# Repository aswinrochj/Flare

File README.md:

# SAFE-NODE — Fail-Safe Real-Time Gas and Fire Safety Network

**Team NEXUS · Team ID M2026-133 · St. Joseph's College of Engineering, Chennai**
VConnecTech Engineering Marathon 2026

SAFE-NODE is a low-cost gas, flame and heat safety network built on the ESP32. Its design rule is that **the system must never fail silently**. An unplugged sensor, a hung controller or a dead radio link is reported as a fault or an offline node, never as "safe".

> **Safety notice.** SAFE-NODE is a student prototype. It is not a certified gas detector (IS/IEC 60079-29-1) or fire alarm (IS 2189), and it must not replace one.

## Documents

| Document | Standard followed | Contents |
|---|---|---|
| [`docs/M2026-133_FailSafeGasFireNetwork_DPR.pdf`](docs/M2026-133_FailSafeGasFireNetwork_DPR.pdf) | Marathon DPR template, IEEE two-column | Problem, objectives O1–O6, design, plan, results |
| [`docs/M2026-133_SAFE-NODE_Technical_Documentation.pdf`](docs/M2026-133_SAFE-NODE_Technical_Documentation.pdf) | IEEE Std 1016 (design), IEEE Std 829 (test) | Schematic, PCB, pin map, BOM, firmware, protocol, test log, anomaly reports |
| [`docs/SRS.md`](docs/SRS.md) | ISO/IEC/IEEE 29148 | Requirements with IDs, traced to objectives and test cases |
| [`test/test-plan.md`](test/test-plan.md) | IEEE Std 829 | Test plan and test case specifications |
| [`test/logs/`](test/logs/) | IEEE Std 829 | Dated test logs and incident reports |
| [`hardware/README.md`](hardware/README.md) | IEEE Std 315, IPC-2221B | KiCad project, fabrication and assembly notes |
| [`docs/references.bib`](docs/references.bib) | IEEE reference style | Bibliography in BibTeX |

## Status (25 November 2026)

| Part | Status |
|---|---|
| Node circuit | Simulated in LabWired. See [`simulation/`](simulation/) |
| Carrier PCB rev 1.0 | KiCad 7 schematic and 2-layer layout complete. DRC shows 0 unconnected pads and 0 clearance errors. Gerbers are ready but no board has been built yet |
| Firmware v0.1 (Arduino) | Runs in simulation. Gas and flame inputs are sampled; a hazard turns on the red LED and buzzer, and a fault turns on the yellow LED |
| Firmware v1.0 (ESP-IDF, FreeRTOS, watchdog, LoRa) | Code complete; builds with ESP-IDF v5.2.3 (no warnings); decision logic unit-tested on a PC. **Not yet run on hardware** |
| Gateway firmware | Code complete; builds with ESP-IDF v5.2.3 (no warnings); node table unit-tested. **Not yet run on hardware** |
| Host: MQTT bridge, SQLite, dashboard, SMS | Complete and tested end to end against a gateway emulator. Not yet run with a real gateway |
| Bench tests TC-1 to TC-9 | Planned for the Implementation Round; scripts in [`test/scripts/`](test/scripts/) |

Open issues are tracked as AR-1 … AR-12 in Section VI-E of the technical documentation. AR-1 and AR-8 are closed in the PCB. AR-2 to AR-7 and AR-10 are addressed in the firmware v1.0 code; they stay open until the bench tests confirm the fixes. Before powering real hardware, read [`hardware/README.md`](hardware/README.md).

## Simulation

| Project | Link |
|---|---|
| `final`: complete node circuit | https://app.labwired.com/p/dharshinir2028/b2b2b0950f8219b71e729534c77f84a7 |
| `final_slider_monitor`: same circuit with slide potentiometers on GPIO32/33 | https://app.labwired.com/p/963436e296210af24c3ec1ab57304f01 |

How to run it and what was verified: [`simulation/README.md`](simulation/README.md).

## Hardware at a glance

| Signal | ESP32 pin | Notes |
|---|---|---|
| MQ-2 AO | GPIO32 (ADC1_CH4) | Through an R1 = 12 kΩ / R2 = 10 kΩ divider (5 V → 2.27 V) |
| Flame AO | GPIO33 (ADC1_CH5) | Module powered from 3V3 |
| DHT22 DATA | GPIO4 | R7 = 10 kΩ pull-up. Read at most once every 2 s |
| Buzzer | GPIO13 | PN2222A low-side driver, R6 = 1 kΩ, D4 flyback |
| LED red / green / yellow | GPIO14 / 16 / 17 | 220 Ω each, for hazard / healthy / fault |
| Battery sense | GPIO35 (ADC1_CH7) | 100 kΩ / 100 kΩ divider |
| RFM95W (SX1276) LoRa | SCK 18, MISO 19, MOSI 23, NSS 5, RST 27, DIO0 26 | 865–867 MHz only (India licence-exempt band) |

Board: 100 × 75 mm, 2 layers. Indicative cost is about ₹2,460 per node (see [`hardware/fab/safe-node-bom.csv`](hardware/fab/safe-node-bom.csv)).

## Quick start (no hardware needed)

```bash
git clone <this repository> && cd safe-node-m2026-133
python3 -m venv .venv && source .venv/bin/activate    # Windows: .venv\Scripts\activate
pip install -r host/requirements-dev.txt
make test        # firmware unit tests (gcc) + host tests (pytest)
make budget      # reproduce the analytical figures of DPR Table X
make demo        # host + emulated gateway with three nodes -> http://127.0.0.1:5000
```

Without `make` (for example on Windows): `cd host && python -m pytest -q`, then `python -m safenode_host --demo --no-mqtt`.

## Repository layout

```
.
├── docs/                 DPR, technical documentation, SRS, figures, references.bib
├── hardware/
│   ├── kicad/            KiCad 7 project (schematic, PCB, symbols, footprints, netlist)
│   ├── fab/              Gerber X2 + Excellon, zipped Gerbers, BOM, placement file
│   ├── plots/            Schematic PDF/PNG, PCB top/bottom/assembly renders
│   └── reports/          KiCad DRC report
├── simulation/           LabWired project links, run procedure, screenshots
├── firmware/
│   ├── node/v0.1/        Arduino prototype (as simulated in LabWired)
│   ├── node/v1.0/        ESP-IDF + FreeRTOS target firmware
│   ├── gateway/          Gateway ESP32 + SX1276
│   ├── components/       Shared: frame protocol, SX1276 driver, board pin map
│   └── test/             Unit tests for the firmware logic (run on a PC)
├── host/                 Serial→MQTT bridge, SQLite, Flask dashboard, SMS queue, gateway emulator
├── test/                 Test plan, dated test logs, log template, test scripts, protocol vectors
├── tools/                DPR budget calculator, vector generator, pcbgen (schematic/PCB generator)
├── .github/              CI workflow, anomaly-report and change-request templates
├── Makefile              test / demo / budget / node / gateway targets
├── LICENSES/             Full licence texts
├── CITATION.cff  CHANGELOG.md  CONTRIBUTING.md  CODE_OF_CONDUCT.md
```

## Dependencies

| Part | Tools and libraries |
|---|---|
| Firmware v0.1 | Arduino IDE 2, *esp32* board package by Espressif |
| Firmware v1.0, gateway | ESP-IDF v5.2 or later (includes FreeRTOS); CI uses v5.2.3 |
| Firmware unit tests | A C99 compiler (`gcc` or `clang`) and `make` |
| Host | Python 3.10+, packages in [`host/requirements.txt`](host/requirements.txt) (`paho-mqtt`, `flask`, `pyserial`, `requests`); Mosquitto MQTT broker (optional); Twilio account for SMS (optional) |
| Hardware | KiCad 7 or later |
| `tools/pcbgen` | KiCad 7 `pcbnew` Python module, Python 3.10+, `numpy` |
| Simulation | Web browser (LabWired, links above) |

## Build and run

**Firmware v0.1 (Arduino):** see [`firmware/node/v0.1/README.md`](firmware/node/v0.1/README.md). In Arduino IDE 2, install the *esp32* board package, open `firmware/node/v0.1/main/main.ino`, select *ESP32 Dev Module* and upload. Serial Monitor at 115200 baud; test commands `G<n>`, `F<n>`, `T<n>`, `H<n>`, `X`/`Y`/`Z`, `R`, `?`.

**Firmware v1.0 and gateway (ESP-IDF v5):**
```bash
. $IDF_PATH/export.sh
cd firmware/node/v1.0             # set a unique node ID in menuconfig -> "SAFE-NODE node"
idf.py set-target esp32
idf.py menuconfig
idf.py build flash monitor
cd ../../gateway && idf.py set-target esp32 build flash
```
Details: [`firmware/node/v1.0/README.md`](firmware/node/v1.0/README.md), [`firmware/gateway/README.md`](firmware/gateway/README.md).

**Host:**
```bash
cd host && pip install -r requirements.txt
python bridge.py --port /dev/ttyUSB0 --config config.example.json     # dashboard at http://127.0.0.1:5000
```
Details: [`host/README.md`](host/README.md).

**Hardware:** open `hardware/kicad/safe-node.kicad_pro` in KiCad 7 or later. To order boards, send `hardware/fab/safe-node-gerbers.zip` to any PCB maker. Settings: 2 layers, 1.6 mm FR-4, HASL.

**Continuous integration:** every push runs the unit tests, checks the protocol vectors and the DPR budget, builds both ESP-IDF projects with ESP-IDF v5.2.3, and compiles the v0.1 sketch ([`.github/workflows/ci.yml`](.github/workflows/ci.yml)).

## Requirement coverage in code

| Objective | Requirements | Implemented in | Verified by (today) |
|---|---|---|---|
| O1 local alarm | FR-01, FR-03–FR-06, PR-01 | `firmware/node/v1.0/main/classifier.c`, `main.c` (sensor, alarm tasks) | `firmware/test/test_classifier.c`; SIM-2 (v0.1) |
| O2 remote alert | FR-22–FR-25, PR-02 | `firmware/node/v1.0/main/radio.c`, `firmware/gateway/`, `host/` | `host/tests/`; analysis `tools/lora_budget.py` |
| O3 offline detection | FR-20, FR-21 | `heartbeat_task`, `firmware/gateway/main/node_table.c` | `test_node_table.c`, `host/tests/test_end_to_end.py` |
| O4 hang recovery | FR-14, FR-15 | `health_task` (conditional watchdog feed), RTC reset counter, NVS event ring | TC-4 on the bench (planned) |
| O5 sensor faults | FR-02, FR-10–FR-13 | `classifier.c`, `selftest.c`, `dht22.c` | `test_classifier.c` |
| O6 cost, backup, isolation | FR-16, PR-03, PR-04, HR-06 | Task priorities and core pinning, low-battery rule | BOM; `tools/lora_budget.py`; TC-6, TC-8 (planned) |

## Team

| Member | Role |
|---|---|
| Dharshini R (Team Lead) | Firmware, RTOS, watchdog, test lead |
| Dheekshitha R | Hardware, power, sensor interfacing |
| Aswin Roch J | LoRa / ESP-NOW, protocol, gateway |
| Anto Prisin D | MQTT bridge, dashboard, SMS |

## Licence

| Part | Licence |
|---|---|
| Firmware, host software, `tools/` | MIT ([`LICENSE`](LICENSE)) |
| Hardware design files (`hardware/`) | CERN-OHL-P-2.0 ([`LICENSES/CERN-OHL-P-2.0.txt`](LICENSES/CERN-OHL-P-2.0.txt)) |
| Documentation (`docs/`, `test/`, `simulation/`) | CC BY 4.0 ([`LICENSES/CC-BY-4.0.txt`](LICENSES/CC-BY-4.0.txt)) |

To cite this work, see [`CITATION.cff`](CITATION.cff).

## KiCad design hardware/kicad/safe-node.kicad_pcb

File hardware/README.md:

# SAFE-NODE carrier board, rev 1.0: hardware documentation

The carrier PCB holds one sensor node: an ESP32-DevKitC V4 in sockets, an RFM95W (SX1276) LoRa module, connectors for the MQ-2, flame and DHT22 modules, a 5 V power input, battery sensing, status LEDs and a buzzer driver.

- Schematic, drawn in KiCad 7 with class letters per IEEE Std 315: [`plots/safe-node-schematic.pdf`](plots/safe-node-schematic.pdf)
- PCB layout, 2-layer, IPC-2221B clearances: [`kicad/safe-node.kicad_pcb`](kicad/safe-node.kicad_pcb)
- Design rationale (divider values, power budget, driver sizing): Section III of [`../docs/M2026-133_SAFE-NODE_Technical_Documentation.pdf`](../docs/M2026-133_SAFE-NODE_Technical_Documentation.pdf)

## Simulation links

The circuit on this board was first simulated in LabWired:

| Project | Link | Contents |
|---|---|---|
| `final` | https://app.labwired.com/p/dharshinir2028/b2b2b0950f8219b71e729534c77f84a7 | Complete node circuit: ESP32, MQ-2, flame, DHT22, buzzer driver, LEDs |
| `final_slider_monitor` | https://app.labwired.com/p/963436e296210af24c3ec1ab57304f01 | Same circuit, with slide potentiometers driving GPIO32/33. Firmware v0.1. Electrical check passed |

Changes from the simulated circuit to this PCB:

| Change | Reason |
|---|---|
| MQ-2 AO goes through R1 = 12 kΩ / R2 = 10 kΩ to GPIO32 | Closes AR-1. Without the divider, up to 5 V reaches a 3.3 V pin |
| Buzzer base resistor raised from 220 Ω to 1 kΩ | Closes AR-8. 2.6 mA base current still saturates the PN2222A |
| LEDs changed to red, green and yellow | Closes AR-8 |
| Added: RFM95W, SMA connector, 5 V input with D5 reverse-polarity protection, JP1, battery sense, decoupling and ADC filter capacitors | Not modelled in the simulation |

Because of the divider, the gas threshold of 1800 counts used in the simulation must be recalibrated for hardware.

## Files

| Path | Contents |
|---|---|
| `kicad/safe-node.kicad_pro` | KiCad 7 project. Open this file |
| `kicad/safe-node.kicad_sch` | Schematic, single A3 sheet |
| `kicad/safe-node.kicad_pcb` | PCB layout: 100 × 75 mm, 2 layers |
| `kicad/safe-node.kicad_sym`, `kicad/safe-node.pretty/` | Project symbol and footprint libraries. The tables reference them through `${KIPRJMOD}` |
| `kicad/safe-node.net` | Exported netlist: 36 parts, 27 nets |
| `fab/gerbers/` | Gerber X2 layers, Excellon PTH/NPTH drill files and drill maps, `.gbrjob` |
| `fab/safe-node-gerbers.zip` | Same files, zipped for upload to a PCB maker |
| `fab/safe-node-bom.csv` | Grouped bill of materials, with function and indicative INR cost for each line |
| `fab/safe-node-pos.csv` | Component placement file |
| `plots/` | Schematic PDF and PNG; PCB top, bottom and assembly renders (PNG, SVG, PDF) |
| `reports/drc.rpt` | KiCad design-rule-check report |

All other footprints come from the standard KiCad 7 libraries.

## Board data

| Item | Value |
|---|---|
| Size and stack-up | 100 × 75 mm, 2 layers, FR-4 1.6 mm, 1 oz copper |
| Clearance / edge clearance | 0.2 mm / 0.3 mm |
| Track width | 0.3 mm signal, 0.6 mm power, 1.0 mm RF (ANT) |
| Vias | 0.8 mm pad, 0.4 mm drill (18 in total) |
| Ground | GND pour on both layers, with thermal reliefs |
| Mounting | 4 × M3 (3.2 mm) holes at the corners |
| Routing | 400 track segments, 1.25 m of track |

## Design-rule check

DRC was run in KiCad 7 (`reports/drc.rpt`).

| Result | Count | Disposition |
|---|---|---|
| Unconnected pads | 0 | — |
| Clearance / short errors | 0 | — |
| Footprint errors | 0 | — |
| `copper_edge_clearance` | 5 | Accepted. J1 is an edge-mount SMA connector and must sit on the board edge |
| `silk_overlap` | 4 | Cosmetic. Reference text touches outline silkscreen; legible on the plots |
| `lib_footprint_issues` | 35 | Environment only. The DRC machine had no global KiCad footprint table. These warnings disappear on a normal KiCad install |

The schematic netlist was compared with the source netlist in `tools/pcbgen/netlist.py`: 27 of 27 nets matched, with 0 differences. The board was routed by the grid router in `tools/pcbgen/router.py`, and every result was then checked with KiCad's own DRC.

## Before you order or power the board

1. **Measure the DevKit row spacing.** The footprint assumes the two 1×19 header rows are 25.4 mm (1.0 in) apart, as on the Espressif ESP32-DevKitC V4. Some clone boards use 22.86 mm or 27.94 mm. Hold the board against a 1:1 print of `plots/pcb-top.pdf` before ordering.
2. **Set the 5 V supply to 5.4 V.** The MQ-2 heater needs 5.0 ± 0.1 V, and D5 (1N5819) drops 0.3–0.45 V. With an adjustable boost module (MT3608), set its output to about 5.4 V, then measure 4.9–5.1 V at J2 pin 1.
3. **Use one power source at a time.** The DevKitC must have only one supply. JP1 joins the board's 5 V rail to the DevKit 5V pin. **Remove JP1 whenever a USB cable is plugged into the DevKit.**
4. **Check the MQ-2 module pin order** against J2 (pin 1 VCC, 2 GND, 3 DO, 4 AO) before plugging it in. DO is not connected.
5. **Connect the antenna before transmitting.** Fit an 865–867 MHz antenna to J1 before running any LoRa firmware.
6. **Check flame-module polarity.** Some modules pull AO low when they see a flame. Confirm on the real module before setting the comparison direction in firmware (AR-9).

## Assembly order

1. Low parts first: resistors R1–R9, diodes D4 and D5 (check the band), and capacitors C3–C7.
2. Then the RFM95W (U2, SMD castellations, hand-solderable with a fine tip), followed by the SMA connector J1.
3. Then Q1 (check the flat face against the silkscreen), the LEDs D1–D3 (long lead = anode, square pad = cathode), the buzzer BZ1 (+ to the 5V pad), and electrolytics C1 and C2 (observe polarity).
4. Last, the two 1×19 female sockets for U1, the pin headers J2–J4, JP1, and the terminal blocks J5 and J6.
5. Before inserting the DevKit, power J5 and check: 5 V at JP1 pin 1; with JP1 fitted and the DevKit inserted, 3.3 V on the +3V3 net; no more than 2.3 V at GPIO32 with the MQ-2 fitted.

## Regenerating the design

The schematic and PCB are generated from one netlist (`tools/pcbgen/netlist.py`). See [`../tools/pcbgen/README.md`](../tools/pcbgen/README.md). If you edit them by hand in KiCad, stop using the generator, or your edits will be overwritten.

## Licence

The hardware design files in this directory are licensed under CERN-OHL-P-2.0 (see [`../LICENSES/CERN-OHL-P-2.0.txt`](../LICENSES/CERN-OHL-P-2.0.txt)).

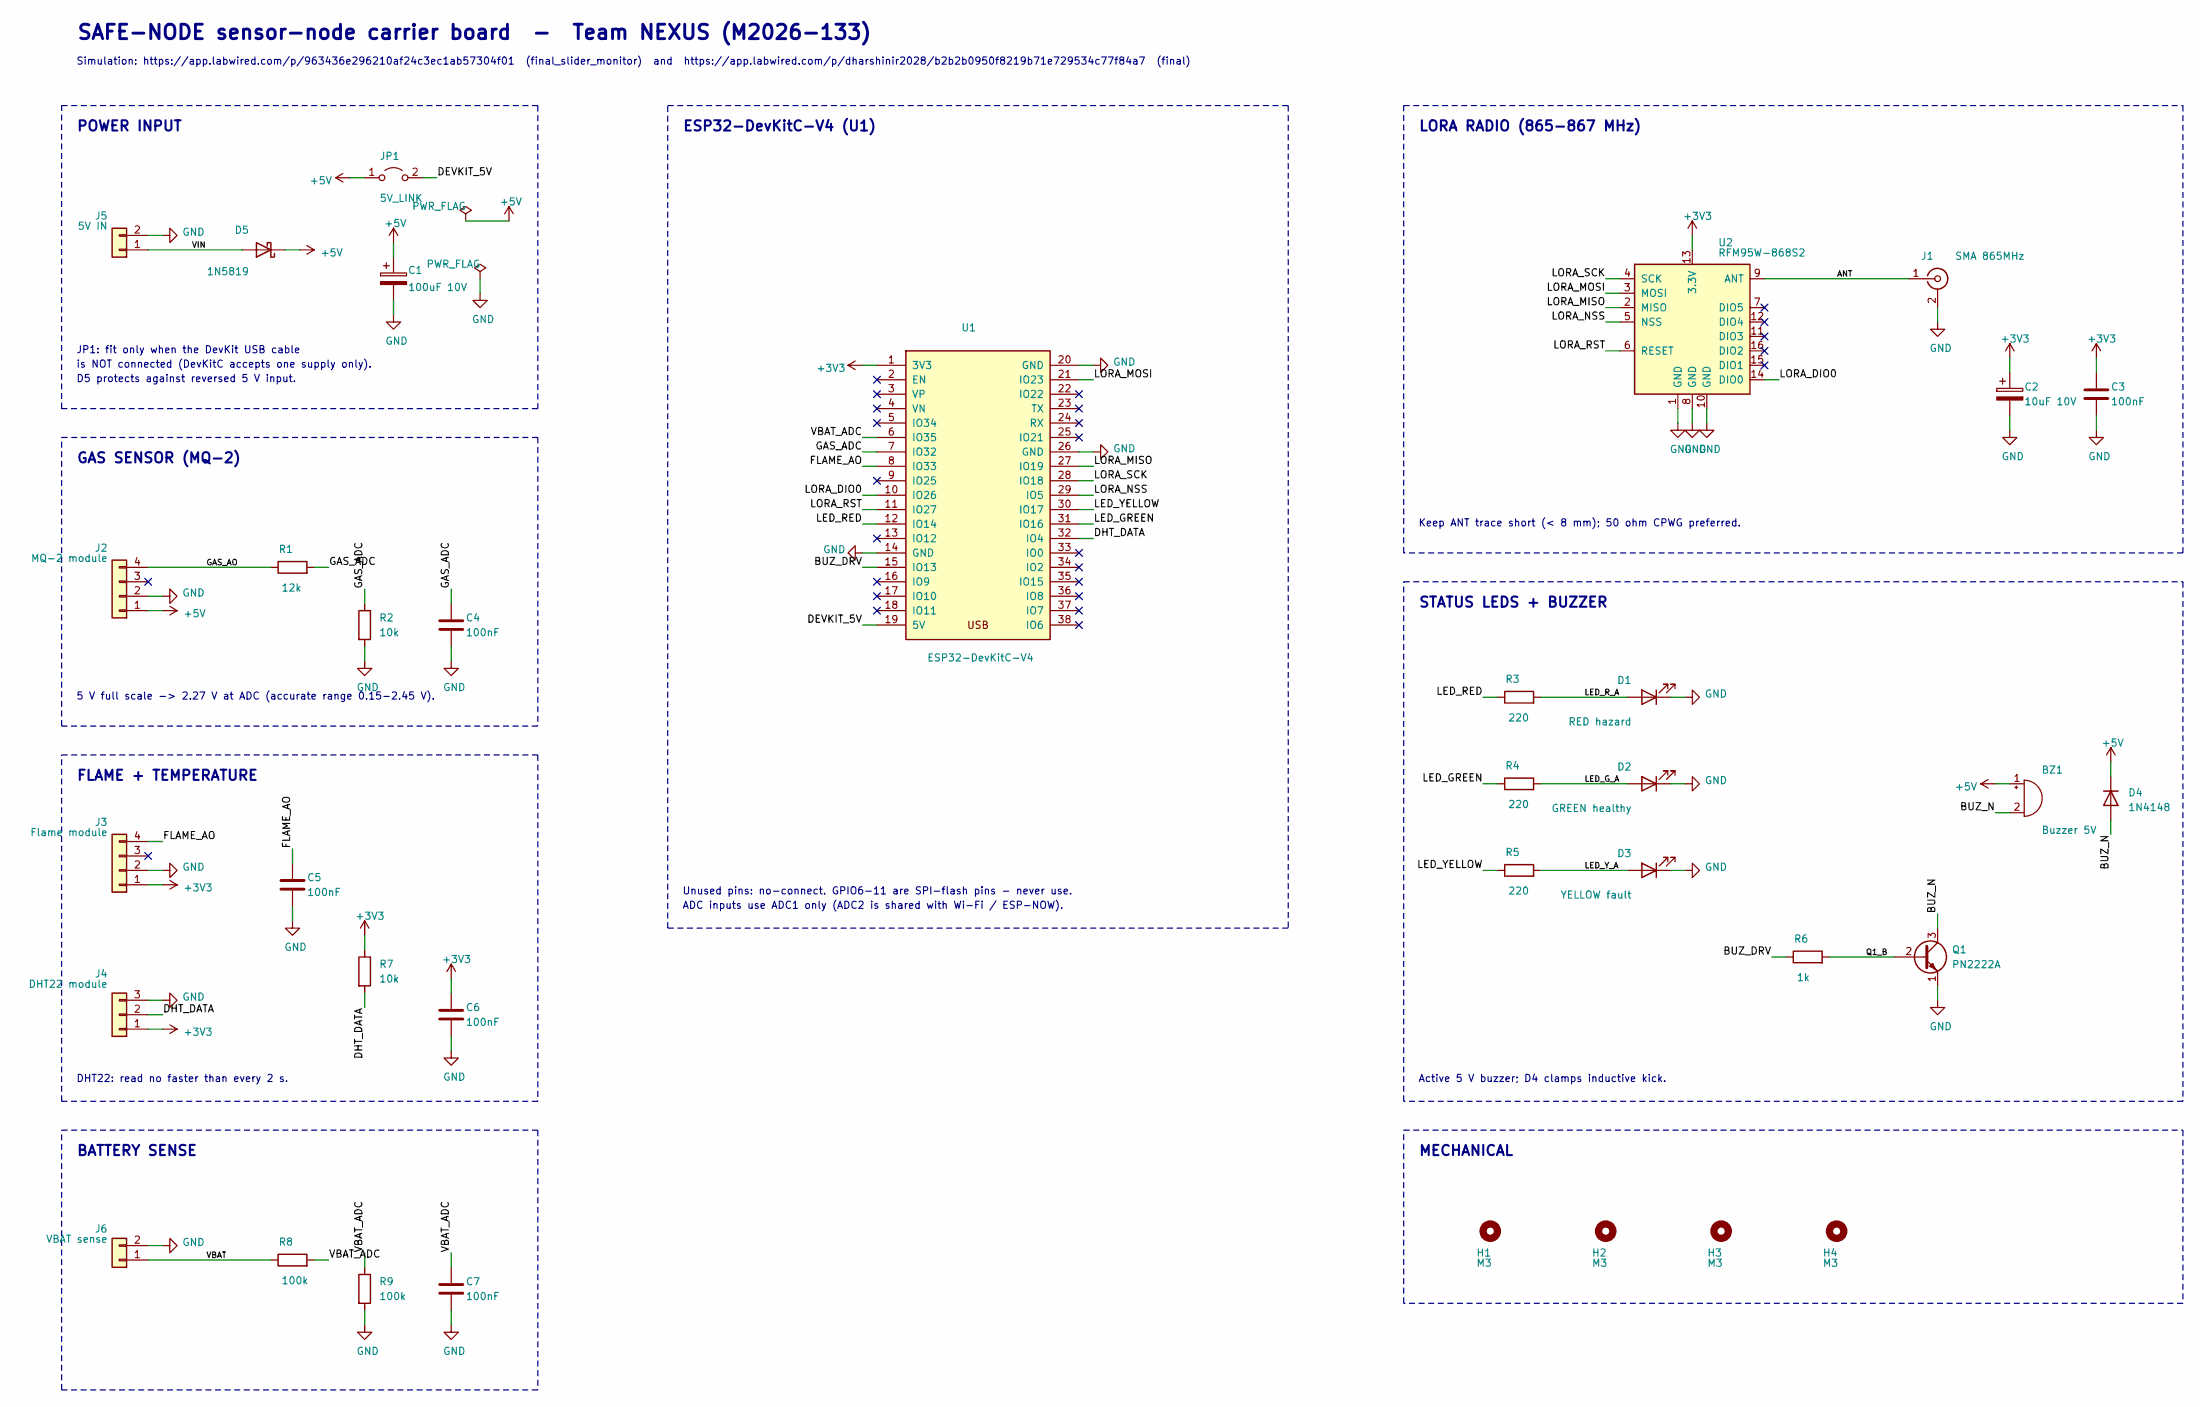
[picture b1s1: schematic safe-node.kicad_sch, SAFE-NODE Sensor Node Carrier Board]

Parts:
BZ1: Buzzer 5V; Buzzer_12x9.5RM7.6
C1: 100uF 10V; CP_Radial_D6.3mm_P2.50mm
C2: 10uF 10V; CP_Radial_D5.0mm_P2.00mm
C3, C4, C5, C6, C7: 100nF; C_Disc_D3.0mm_W1.6mm_P2.50mm
D1: RED hazard; LED_D5.0mm
D2: GREEN healthy; LED_D5.0mm
D3: YELLOW fault; LED_D5.0mm
D4: 1N4148; D_DO-35_SOD27_P7.62mm_Horizontal
D5: 1N5819; D_DO-41_SOD81_P10.16mm_Horizontal
H1, H2, H3, H4: M3; MountingHole_3.2mm_M3
J1: SMA 865MHz; SMA_Amphenol_132289_EdgeMount
J2: MQ-2 module; PinHeader_1x04_P2.54mm_Vertical
J3: Flame module; PinHeader_1x04_P2.54mm_Vertical
J4: DHT22 module; PinHeader_1x03_P2.54mm_Vertical
J5: 5V IN; TerminalBlock_bornier-2_P5.08mm
J6: VBAT sense; PinHeader_1x02_P2.54mm_Vertical
JP1: 5V_LINK; PinHeader_1x02_P2.54mm_Vertical
Q1: PN2222A; TO-92_Inline
R1: 12k; R_Axial_DIN0207_L6.3mm_D2.5mm_P7.62mm_Horizontal
R2, R7: 10k; R_Axial_DIN0207_L6.3mm_D2.5mm_P7.62mm_Horizontal
R3, R4, R5: 220; R_Axial_DIN0207_L6.3mm_D2.5mm_P7.62mm_Horizontal
R6: 1k; R_Axial_DIN0207_L6.3mm_D2.5mm_P7.62mm_Horizontal
R8, R9: 100k; R_Axial_DIN0207_L6.3mm_D2.5mm_P7.62mm_Horizontal
U1: ESP32-DevKitC-V4; ESP32-DevKitC-V4_Socket
U2: RFM95W-868S2; HOPERF_RFM9XW_SMD

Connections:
+3V3: C2.1, C3.1, C6.1, J3.1, J4.1, R7.1, U1.1 (3V3), U2.13 (3.3V)
+5V: BZ1.1 (+), C1.1, D4.1 (K), D5.1 (K), J2.1, JP1.1 (A)
ANT: J1.1 (In), U2.9 (ANT)
BUZ_DRV: R6.1, U1.15 (IO13)
BUZ_N: BZ1.2 (-), D4.2 (A), Q1.3 (C)
DEVKIT_5V: JP1.2 (B), U1.19 (5V)
DHT_DATA: J4.2, R7.2, U1.32 (IO4)
FLAME_AO: C5.1, J3.4, U1.8 (IO33)
GAS_ADC: C4.1, R1.2, R2.1, U1.7 (IO32)
GAS_AO: J2.4, R1.1
GND: C1.2, C2.2, C3.2, C4.2, C5.2, C6.2, C7.2, D1.1 (K), D2.1 (K), D3.1 (K), J1.2 (Ext), J2.2, J3.2, J4.3, J5.2, J6.2, Q1.1 (E), R2.2, R9.2, U1.14 (GND), U1.20 (GND), U1.26 (GND), U2.1 (GND), U2.8 (GND), U2.10 (GND)
LED_GREEN: R4.1, U1.31 (IO16)
LED_G_A: D2.2 (A), R4.2
LED_RED: R3.1, U1.12 (IO14)
LED_R_A: D1.2 (A), R3.2
LED_YELLOW: R5.1, U1.30 (IO17)
LED_Y_A: D3.2 (A), R5.2
LORA_DIO0: U1.10 (IO26), U2.14 (DIO0)
LORA_MISO: U1.27 (IO19), U2.2 (MISO)
LORA_MOSI: U1.21 (IO23), U2.3 (MOSI)
LORA_NSS: U1.29 (IO5), U2.5 (NSS)
LORA_RST: U1.11 (IO27), U2.6 (RESET)
LORA_SCK: U1.28 (IO18), U2.4 (SCK)
Q1_B: Q1.2 (B), R6.2
VBAT: J6.1, R8.1
VBAT_ADC: C7.1, R8.2, R9.1, U1.6 (IO35)
VIN: D5.2 (A), J5.1

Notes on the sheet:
SAFE-NODE sensor-node carrier board - Team NEXUS (M2026-133)
Simulation: https://app.labwired.com/p/963436e296210af24c3ec1ab57304f01 (final_slider_monitor) and https://app.labwired.com/p/dharshinir2028/b2b2b0950f8219b71e729534c77f84a7 (final)
POWER INPUT
JP1: fit only when the DevKit USB cable
is NOT connected (DevKitC accepts one supply only).
D5 protects against reversed 5 V input.
ESP32-DevKitC-V4 (U1)
Unused pins: no-connect. GPIO6-11 are SPI-flash pins - never use.
ADC inputs use ADC1 only (ADC2 is shared with Wi-Fi / ESP-NOW).
GAS SENSOR (MQ-2)
5 V full scale -> 2.27 V at ADC (accurate range 0.15-2.45 V).
FLAME + TEMPERATURE
DHT22: read no faster than every 2 s.
BATTERY SENSE
LORA RADIO (865-867 MHz)
Keep ANT trace short (< 8 mm); 50 ohm CPWG preferred.
STATUS LEDS + BUZZER
Active 5 V buzzer; D4 clamps inductive kick.
MECHANICAL

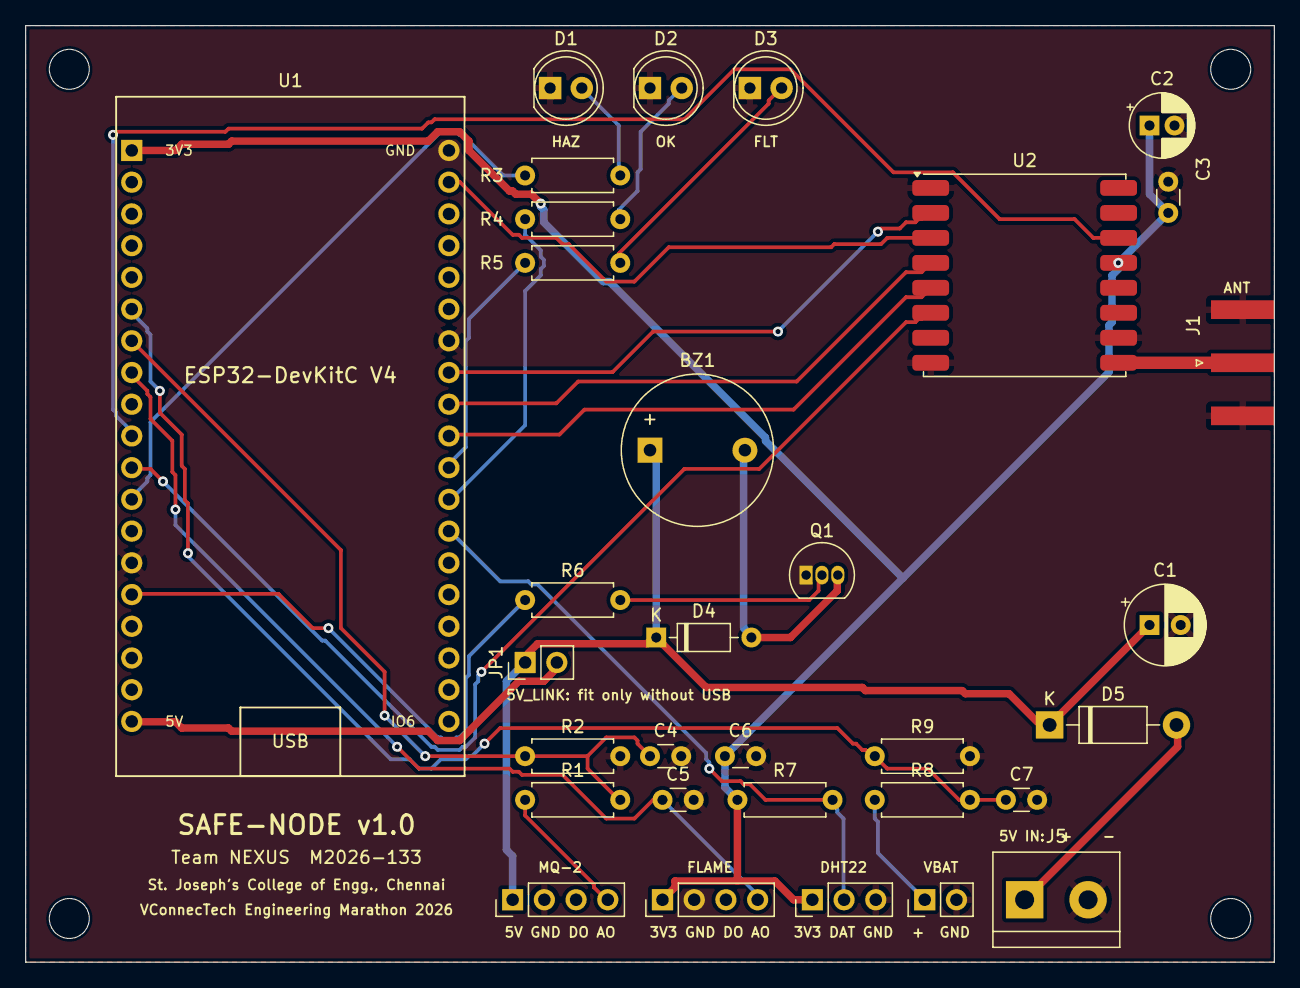
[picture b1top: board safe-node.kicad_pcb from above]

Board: 2 copper layers, 100.0 x 75.0 mm, 36 parts (0 on the bottom side), 27 nets.

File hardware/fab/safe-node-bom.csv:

Item,References,Qty,Value,Footprint,Function,Indicative cost INR (Nov 2026),Notes
1,U1,1,ESP32-DevKitC-V4,ESP32-DevKitC-V4_Socket,"Espressif ESP32-DevKitC V4 (WROOM-32) on 2x19 female sockets, rows 25.4 mm apart",450,"Two 1x19 2.54 mm female sockets, rows 25.4 mm apart"
2,U2,1,RFM95W-868S2,HOPERF_RFM9XW_SMD,"HopeRF SX1276 LoRa module, operated at 865-867 MHz",690,
3,J1,1,SMA 865MHz,SMA_Amphenol_132289_EdgeMount,SMA edge-mount antenna connector,100 (incl. antenna),
4,J2,1,MQ-2 module,PinHeader_1x04_P2.54mm_Vertical,"MQ-2 module: VCC, GND, DO (unused), AO",110 (module),
5,J3,1,Flame module,PinHeader_1x04_P2.54mm_Vertical,"IR flame module: VCC, GND, DO (unused), AO",60 (module),
6,J4,1,DHT22 module,PinHeader_1x03_P2.54mm_Vertical,"DHT22/AM2302: VCC, DATA, GND",200 (module),
7,J5,1,5V IN,TerminalBlock_bornier-2_P5.08mm,External 5 V input (adapter or 18650 + TP4056 + MT3608 module),,
8,J6,1,VBAT sense,PinHeader_1x02_P2.54mm_Vertical,Battery cell voltage for monitoring,,
9,JP1,1,5V_LINK,PinHeader_1x02_P2.54mm_Vertical,Fit only when the DevKit USB cable is NOT connected,,2-pin header + jumper shunt
10,Q1,1,PN2222A,TO-92_Inline,"NPN buzzer driver, TO-92 E-B-C",,
11,D1,1,RED hazard,LED_D5.0mm,5 mm red LED,,
12,D2,1,GREEN healthy,LED_D5.0mm,5 mm green LED,,
13,D3,1,YELLOW fault,LED_D5.0mm,5 mm yellow LED,,
14,D4,1,1N4148,D_DO-35_SOD27_P7.62mm_Horizontal,Buzzer flyback diode,,
15,D5,1,1N5819,D_DO-41_SOD81_P10.16mm_Horizontal,Reverse-polarity protection,,Set boost/adapter to 5.4 V so the MQ-2 heater sees 5.0 V after the diode drop
16,BZ1,1,Buzzer 5V,Buzzer_12x9.5RM7.6,"Active 5 V buzzer, 12 mm",,
17,R1,1,12k,R_Axial_DIN0207_L6.3mm_D2.5mm_P7.62mm_Horizontal,"MQ-2 divider, top",,
18,R2 R7,2,10k,R_Axial_DIN0207_L6.3mm_D2.5mm_P7.62mm_Horizontal,"R2: MQ-2 divider, bottom; open-wire pull-down; R7: DHT22 pull-up (omit if module has one)",,R7 is DNP if the DHT22 module already has a pull-up
19,R3 R4 R5,3,220,R_Axial_DIN0207_L6.3mm_D2.5mm_P7.62mm_Horizontal,LED current limit,,
20,R6,1,1k,R_Axial_DIN0207_L6.3mm_D2.5mm_P7.62mm_Horizontal,Q1 base resistor,,
21,R8 R9,2,100k,R_Axial_DIN0207_L6.3mm_D2.5mm_P7.62mm_Horizontal,"R8: Battery divider, top; R9: Battery divider, bottom",,
22,C1,1,100uF 10V,CP_Radial_D6.3mm_P2.50mm,5 V bulk,,
23,C2,1,10uF 10V,CP_Radial_D5.0mm_P2.00mm,RFM95W bulk,,
24,C3 C4 C5 C6 C7,5,100nF,C_Disc_D3.0mm_W1.6mm_P2.50mm,C3: RFM95W decoupling; C4: ADC input filter; C5: ADC input filter; C6: DHT22 decoupling; C7: ADC input filter,,
25,H1 H2 H3 H4,4,M3,MountingHole_3.2mm_M3,Mounting hole,,"Holes only, no part"

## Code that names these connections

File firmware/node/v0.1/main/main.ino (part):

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 */

// ---------------- Pin map (Technical Documentation Table IV) ----------------
const int PIN_GAS_ADC    = 32;   // MQ-2 AO (slider in simulation)
const int PIN_FLAME_ADC  = 33;   // flame AO (slider in simulation)
const int PIN_DHT        = 4;    // DHT22 data (not read in v0.1, AR-3)
const int PIN_BUZZER     = 13;   // PN2222A base via resistor
const int PIN_LED_RED    = 14;   // hazard
const int PIN_LED_GREEN  = 16;   // healthy
const int PIN_LED_YELLOW = 17;   // fault

// ---------------- Thresholds ----------------
const int   GAS_THRESHOLD   = 1800;   // ADC counts (slider connected directly)
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  Serial.begin(115200);
  delay(100);

  pinMode(PIN_GAS_ADC, INPUT);
  pinMode(PIN_FLAME_ADC, INPUT);
  pinMode(PIN_DHT, INPUT_PULLUP);
  pinMode(PIN_BUZZER, OUTPUT);
  pinMode(PIN_LED_RED, OUTPUT);
  pinMode(PIN_LED_GREEN, OUTPUT);
  pinMode(PIN_LED_YELLOW, OUTPUT);

  digitalWrite(PIN_BUZZER, LOW);
  digitalWrite(PIN_LED_RED, LOW);
  digitalWrite(PIN_LED_YELLOW, LOW);

  Serial.println();
  Serial.println("==============================================");
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  Serial.println("[CHECK] Temperature sensor  OK");
  Serial.println("[CHECK] Outputs ........... OK");

  digitalWrite(PIN_LED_GREEN, HIGH);
  Serial.println("[SYSTEM] SAFE MODE ACTIVE");
  Serial.println("Type ? for test commands.");
}
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  }

  // Sample both analog inputs on every pass (AR-10: floods the log)
  gasValue   = analogRead(PIN_GAS_ADC);
  flameValue = analogRead(PIN_FLAME_ADC);
  flameDetected = flameValue >= FLAME_THRESHOLD;
  Serial.print("Gas ADC: ");
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// Hazard takes priority over fault.
void updateOutputs() {
  if (hazardDetected) {
    digitalWrite(PIN_LED_GREEN, LOW);
    digitalWrite(PIN_LED_YELLOW, LOW);
    digitalWrite(PIN_LED_RED, HIGH);
    digitalWrite(PIN_BUZZER, HIGH);
    if (!redLedState) {
      Serial.println("[OUTPUT] RED LED ON");
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    if (buzzerState) {
      Serial.println("[OUTPUT] BUZZER OFF");
    }
    digitalWrite(PIN_LED_RED, LOW);
    digitalWrite(PIN_BUZZER, LOW);
    redLedState = false;
    buzzerState = false;

    if (systemFault) {
      digitalWrite(PIN_LED_GREEN, LOW);
      digitalWrite(PIN_LED_YELLOW, HIGH);
    } else {
      digitalWrite(PIN_LED_YELLOW, LOW);
      digitalWrite(PIN_LED_GREEN, HIGH);
    }
  }
}
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

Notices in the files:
firmware/node/v0.1/main/main.ino:
SPDX-License-Identifier: MIT
